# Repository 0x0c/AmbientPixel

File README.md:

# AmbientPixel a.k.a SmartPixel

ピクセルのメタファを持ち合わせる三角形のデバイス。

ディスプレイのピクセルを一つ一つ取り出し、再構成することであなただけの情報提示装置として振る舞います。

https://vimeo.com/143473565

## Requirements

- Arduino
- 赤外線LED
- [赤外線リモコン受信モジュール](http://akizukidenshi.com/catalog/g/gI-00622/)
- [マイコン内蔵RGB LED](http://akizukidenshi.com/catalog/g/gM-08414/)

## Dependencies

- C++拡張
	- [StandardCplusplus](https://github.com/0x0c/StandardCplusplus)
- 赤外線通信ライブラリ（修正版）
	- [skInfraredCOM](https://github.com/0x0c/skInfraredCOM)
- フルカラーLED制御ライブラリ
	- [Adafruit_NeoPixel](https://github.com/adafruit/Adafruit_NeoPixel)
	
## Getting Started

Arduinoで動作するプログラムを開発する前に幾つか追加しなければならないライブラリがある。

1. `StandartCplusplus`と`skInfraredCOM`、`Adafruit_NeoPixel`をArduinoのライブラリに追加する
2. `AmbientPixel`のリポジトリをcloneし、Arduinoのライブラリに追加する

## Hardware
###　プロトタイプ1号
縦にした時、Arduino Pro Miniが地面につく辺を基準とする。
LEDが付いている方を正面とする。

- 構成
	- Arduino Pro Mini 3.3V 8MHz
	- マイコン内蔵ＲＧＢＬＥＤモジュール（AE-WS2812B）
	- 赤外線LED 3個
	- 赤外線リモコン受信モジュール 3個
	- 電池ソケット（JST PH 2P）
	- 足用のピンヘッダ 3本
- ピン配置(PIO)
	- 赤外線LED→基準から右回りで2, 3, 4
	- 受信モジュール→基準から右回りで11, 12, 13
	- LEDのデータ線→10
- サイズ
	- 一辺 : 65.8 mm
	- 高さ : 56.8 mm
	
###　プロトタイプ2号
P板で発注した基板を用いた試作。
JSTコネクタが上、コネクタのプリントがされている方を正面とする。
フルカラーLEDのピン配置をミスったので、DIとDOを適当な導線でつなぐ必要がある。
Arduino Pro Mini 3.3V 8MHzとArduino Pro Mini 5.0V 16MHzが混在。もしかしたら、3.3V 8MHzを調達しなおし、ハンダ付けし直す必要が有るかもしれない。
動作周波数をすべて同じにしたい。

電源スイッチを取り付け忘れたので、後でハンダ付けする必要がある。

- サイズ
	- 一辺 : 65.8 mm
	- 高さ : 56.8 mm

### パケット

`Docs/markdown/Packet.md`を参照

### 伝搬アルゴリズム

ブロードキャストし、デバイスIDが一致するデバイスが受理する

## License

GNU General Public License

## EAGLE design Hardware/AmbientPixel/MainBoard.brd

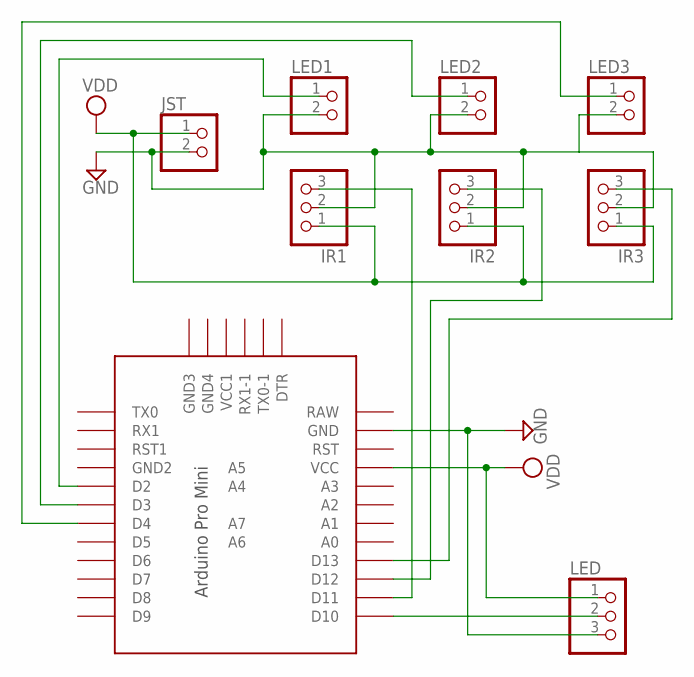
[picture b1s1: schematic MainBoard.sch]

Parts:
IR1, IR2, IR3: PINHD-1X3; 1X03
JST: PINHD-1X2/90; 1X02/90
LED: PINHD-1X3; 1X03
LED1, LED2, LED3: PINHD-1X2; 1X02
U$1: PRO-MINI-2

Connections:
GND: IR1.2, IR2.2, IR3.2, JST.2, LED.3, LED1.2, LED2.2, LED3.2, U$1.GND
unnamed: LED.2, U$1.D10
unnamed: LED1.1, U$1.D2
unnamed: LED2.1, U$1.D3
unnamed: LED3.1, U$1.D4
unnamed: IR1.3, U$1.D11
unnamed: IR2.3, U$1.D12
unnamed: IR3.3, U$1.D13
VDD: IR1.1, IR2.1, IR3.1, JST.1, LED.1, U$1.VCC

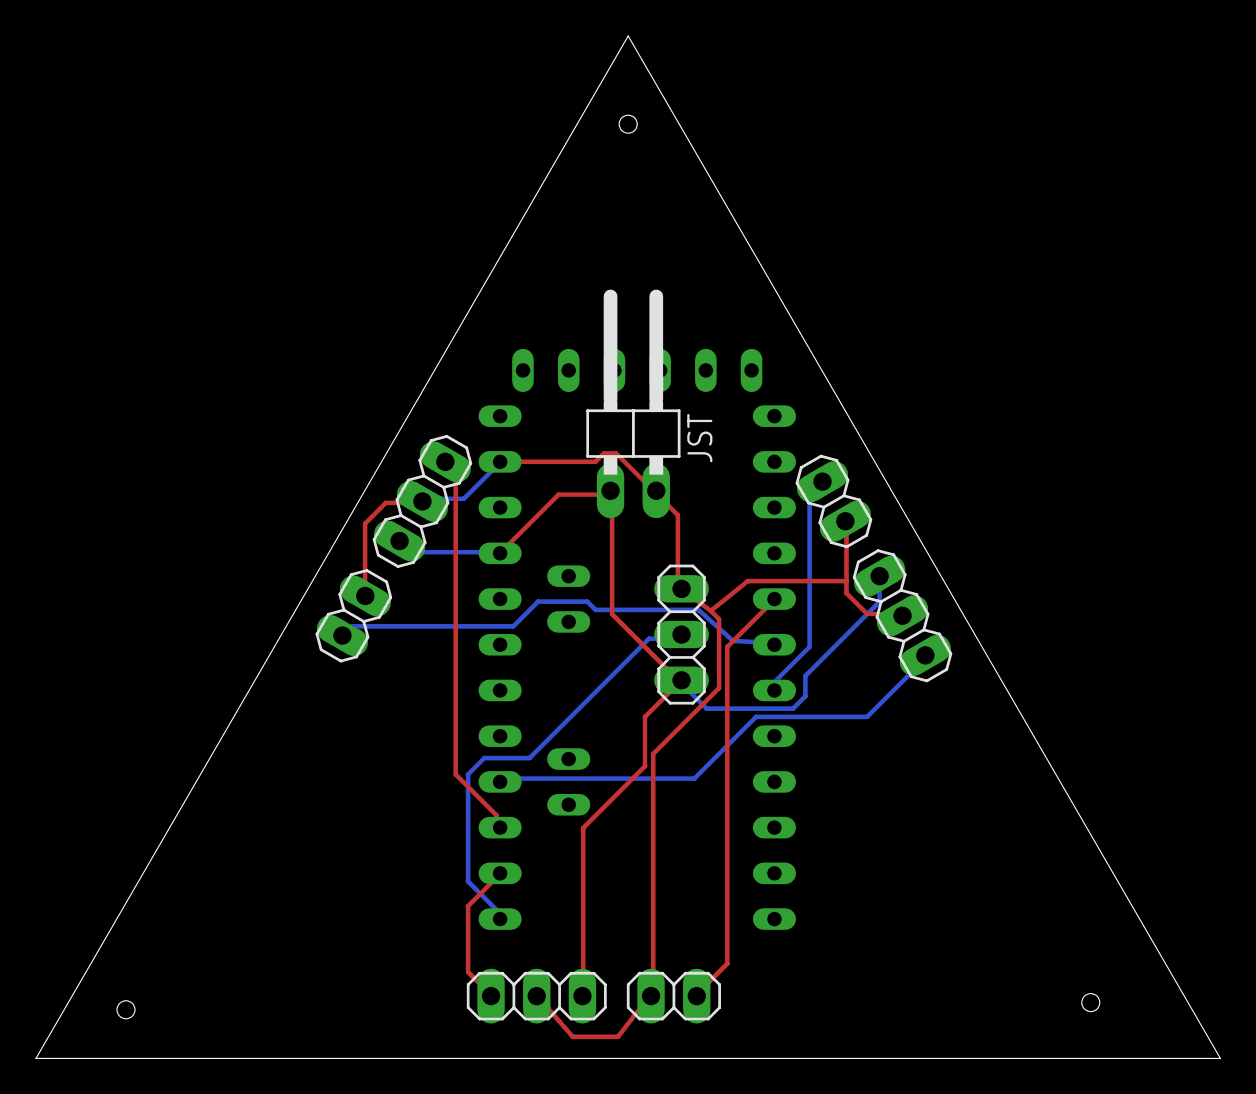
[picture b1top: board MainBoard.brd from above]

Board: 2 copper layers, 65.8 x 56.8 mm, 9 parts (1 on the bottom side), 9 nets.

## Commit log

2015-08-06 fix for Arduino1.6.5
2015-08-06 add gitignore
2015-08-06 add readme
2015-08-18 fix readme
2015-08-18 add documents
2015-08-19 テストプロジェクトの追加
2015-08-19 コメントなど追加
2015-08-19 add photo
2015-08-19 fix typo
2015-08-21 add eagle project
2015-08-21 スケジュールの追加
2015-08-21 p板に納品したファイルの追加
2015-08-21 add app
2015-08-21 add design
2015-08-21 update gitignore
2015-08-21 add comment
2015-08-23 パターンについて月
2015-08-24 add images
2015-08-24 update image
2015-08-24 use uint8_t
2015-08-24 fix coding style
2015-08-24 add firmware project(mock)
2015-08-24 コメント追記
2015-08-24 Portクラスを追加してみた
2015-08-25 グラデーションのテストプロジェクトの追加
2015-08-27 色メソッドの実装switch
2015-08-27 色メソッドの実装7色switch
2015-08-28 7色実装
2015-08-28 サンプルの修正
2015-08-28 色変更メソッドの追加
2015-08-28 コンパイルエラーの修正
2015-08-30 いろいろ
2015-08-30 namespaceの追加
2015-08-30 メソッド名の規則の修正
2015-09-12 サンプルプロジェクトの修正
2015-09-12 podfileの追加
2015-09-12 サンプルプロジェクトの追加
2015-09-14 仕様書のfix
2015-09-16 update docs
2015-09-18 add classes
2015-09-18 Add top view.
2015-09-19 udpate docs and classes
2015-09-19 新しい仕様に追従
2015-09-19 update doc
2015-09-19 add simulator
2015-09-19 fix simulator
2015-09-20 bug fix
2015-09-20 ファイルの追加
2015-09-20 add makefile
2015-09-20 フラグの変更
2015-09-20 fix API and firmware
2015-09-20 print log in simulator
2015-09-20 update xcode proj
2015-09-20 remove log
2015-09-20 fix log message
2015-09-20 Packetにdumpメソッドを追加
2015-09-20 remove examples
2015-09-20 use pods
2015-09-20 fix compile error
2015-09-20 ファームウェアの実装
2015-09-23 設定画面の実装
2015-09-23 定数の並び順の変更
2015-09-24 ファームウェアの更新
2015-09-24 パケットの仕様変更に伴うPortクラスの追加。
2015-09-24 fix interface
2015-09-27 シミュレータにAccept処理の実装
2015-09-27 シミュレータの実装
2015-09-27 コメントの追加
2015-09-27 表示の修正
2015-09-27 逆引きメソッドの追加
2015-09-27 パケットに応じた処理の実装
2015-09-27 リセットパケットの実装
2015-09-28 実験用プロジェクトの追加
2015-09-28 通信機能の実装
2015-09-28 相互通信の実装
2015-09-28 フラグに応じてLEDの点灯させる
2015-09-29 ユースケース追加
2015-09-29 写真追加
2015-10-11 add design file
2015-10-12 ブロードキャスト版
2015-10-12 非表示からグローして立ち上がる
2015-10-12 色取得メソッドのバグ修正
2015-10-12 Yellowの削除
2015-10-12 フォワード消去
2015-10-12 マスターのfirmware(テスト用)
2015-10-13 add movie and images
2015-10-13 update firmware
2015-10-17 add terminal view
2015-10-17 remove forward control
2015-10-17 add keynote
2015-10-18 firmware optimizeation
2015-10-19 add dependences
2015-10-19 stability improvement
2015-10-19 test app
2015-10-21 bug fix.
2015-10-21 add icon image
2015-10-21 remove simulator
2015-10-24 add license
2019-05-08 fixed misspelled words
